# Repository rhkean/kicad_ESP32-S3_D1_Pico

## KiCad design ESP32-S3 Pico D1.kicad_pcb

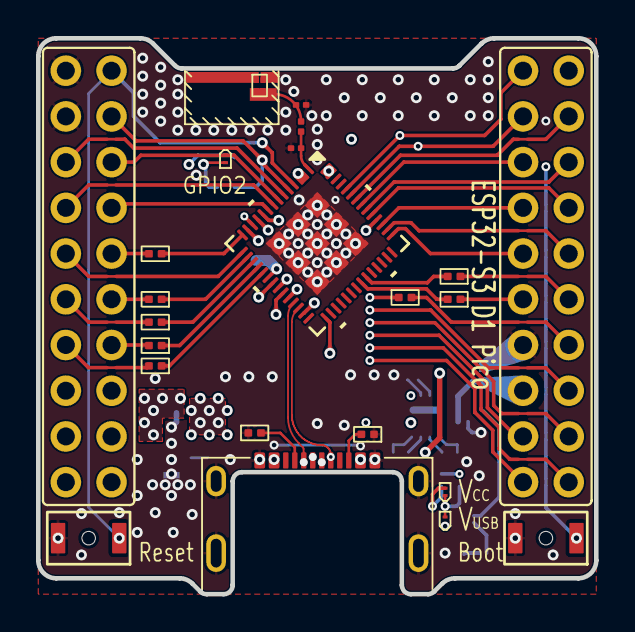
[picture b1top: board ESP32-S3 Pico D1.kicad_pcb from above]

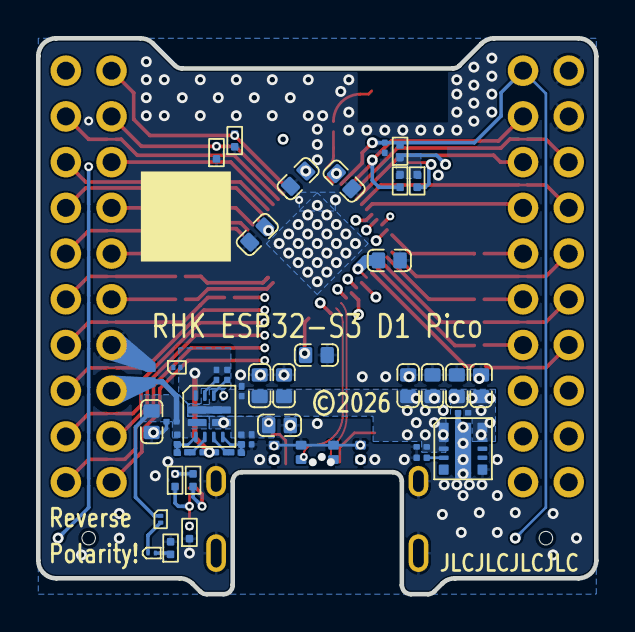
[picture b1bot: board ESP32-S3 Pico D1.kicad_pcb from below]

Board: 6 copper layers, 31.0 x 30.9 mm, 69 parts (47 on the bottom side), 65 nets.

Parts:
ANT401: 2450AT07A0100; Chip Antenna 0402
C401, C402, C403, C404, C405, C501, C503, C507, C508, C509, C510, C513, C514: 22uF; C_0603_Dense
C406, C407: DNP; C_0201_Dense
C502, C504, C505, C506, C511, C512, C601: 0.1uF; C_0201_Dense
CN501: GT-USB-7014D; USB_C_Receptacle_G-Switch-GT-USB-7014D
D501, D502, D505: D15V0H1U2LP-7B; DFN1006-2
D503, D504: SZESD7241N2T5G; DFN1006-2
D506, D601: PMEG4002ESFYL; DFN0603-2
LED601: Blue; LED_0201-2
LED602: Green; LED_0201-2
LED603: Orange; LED_0201-2
LED604: Red; LED_0201-2
R401, R402, R403, R404, R405, R406, R407, R408: 33R; R_0201_Nominal
R409, R410, R501, R502, R601, R602, R604, R605, R606: 5k1; R_0201_Nominal
R411: 0R; R_0201_Dense
R503, R506, R509: 100k; R_0201_Dense
R504, R505, R507, R508, R510: 26k1; R_0201_Dense
R603, R607: 470R; R_0201_Nominal
SW601, SW602: SPST-NO; SW_SPST_B3U_series
U201: ESP32-S3_D1_Pico
U401: ESP32-S3-PICO-1-N8R2; ESP32-S3-Pico-1
U501: TPS2121; VQHN-HR-12
U502: TPSM82903; uSIP-11_3.0x2.8

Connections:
/+5V_{EXT}: C501.1, C502.1, D505.1 (K), D601.1 (K), R506.1, U201.28 (+5V_{EXT}), U501.2 (IN2)
/ESP32-S3 Pico D1-Main/+3V3: C401.1, C402.1, C403.1, C404.1, C405.1, C512.1, C513.1, C514.1, R601.1, R602.1, R603.1, R604.2, R606.2, U201.8 (+3V3_{out}), U201.18 (+3V3), U401.2 (VDD3P3), U401.3 (VDD3P3), U401.20 (VDD3P3_RTC), U401.29 (VDD_SPI), U401.46 (VDD3P3_CPU), U401.55 (VDDA), U401.56 (VDDA), U502.9 (VOUT), U502.10 (VOUT)
/ESP32-S3 Pico D1-Main/+5V_{FUSED}: C506.1, C507.1, C508.1, C509.1, C510.1, C511.1, U201.9 (+5V_{FUSED_{out}}), U501.1 (OUT), U501.8 (OUT), U502.1 (VIN), U502.2 (VIN), U502.3 (EN)
/ESP32-S3 Pico D1-Main/EN/~Reset: C601.1, R601.2, SW601.1, U201.11 (EN/~RST), U401.4 (CHIP_PU)
/ESP32-S3 Pico D1-Main/ESP32-S3-PICO-1/GPIO09: R401.1, U401.14 (GPIO09)
/ESP32-S3 Pico D1-Main/ESP32-S3-PICO-1/GPIO11: R402.1, U401.16 (GPIO11)
/ESP32-S3 Pico D1-Main/ESP32-S3-PICO-1/GPIO12: R403.1, U401.17 (GPIO12)
/ESP32-S3 Pico D1-Main/ESP32-S3-PICO-1/GPIO13: R404.1, U401.18 (GPIO13)
/ESP32-S3 Pico D1-Main/ESP32-S3-PICO-1/GPIO14: R405.1, U401.19 (GPIO14)
/ESP32-S3 Pico D1-Main/ESP32-S3-PICO-1/GPIO21: R406.1, U401.27 (GPIO21)
/ESP32-S3 Pico D1-Main/ESP32-S3-PICO-1/RF_Feed: ANT401.1 (Feed), ANT401.4 (Feed), C407.1, R411.2
/ESP32-S3 Pico D1-Main/ESP32-S3-PICO-1/RF_In: C406.1, R411.1, U401.1 (LNA_IN)
/ESP32-S3 Pico D1-Main/ESP32-S3-PICO-1/USB_D+: CN501.A6 (D+), CN501.B6 (D+), D503.1 (A1), U401.26 (GPIO20/USB_D+)
/ESP32-S3 Pico D1-Main/ESP32-S3-PICO-1/USB_D-: CN501.A7 (D-), CN501.B7 (D-), D504.1 (A1), U401.25 (GPIO19/USB_D-)
/ESP32-S3 Pico D1-Main/IO00: R602.2, SW602.1, U201.12 (IO00), U401.5 (GPIO00)
/ESP32-S3 Pico D1-Main/IO01: U201.3 (IO01), U401.6 (GPIO01)
/ESP32-S3 Pico D1-Main/IO02: LED601.1 (K), U201.13 (IO02), U401.7 (GPIO02)
/ESP32-S3 Pico D1-Main/IO03: U201.4 (IO03), U401.8 (GPIO03)
/ESP32-S3 Pico D1-Main/IO04: U201.14 (IO04), U401.9 (GPIO04)
/ESP32-S3 Pico D1-Main/IO05: U201.20 (I005), U401.10 (GPIO05)
/ESP32-S3 Pico D1-Main/IO06: U201.19 (IO06), U401.11 (GPIO06)
/ESP32-S3 Pico D1-Main/IO07: U201.10 (IO07), U401.12 (GPIO07)
/ESP32-S3 Pico D1-Main/IO08: U201.30 (IO08), U401.13 (GPIO08)
/ESP32-S3 Pico D1-Main/IO09: R401.2, U201.15 (IO09)
/ESP32-S3 Pico D1-Main/IO10: U201.5 (IO10), U401.15 (GPIO10)
/ESP32-S3 Pico D1-Main/IO11: R402.2, U201.16 (IO11)
/ESP32-S3 Pico D1-Main/IO12: R403.2, U201.6 (IO12)
/ESP32-S3 Pico D1-Main/IO13: R404.2, U201.17 (IO13)
/ESP32-S3 Pico D1-Main/IO14: R405.2, U201.7 (IO14)
/ESP32-S3 Pico D1-Main/IO15: U201.40 (IO15), U401.21 (XTAL_32K_P/GPIO15)
/ESP32-S3 Pico D1-Main/IO16: U201.39 (IO16), U401.22 (XTAL_32K_N/GPIO16)
/ESP32-S3 Pico D1-Main/IO17: U201.29 (IO17), U401.23 (GPIO17)
/ESP32-S3 Pico D1-Main/IO18: U201.38 (IO18), U401.24 (GPIO18)
/ESP32-S3 Pico D1-Main/IO21: R406.2, U201.37 (IO21)
/ESP32-S3 Pico D1-Main/IO38: U201.25 (IO38), U401.43 (GPIO38)
/ESP32-S3 Pico D1-Main/IO39: U201.35 (IO39), U401.44 (MTCK/GPIO39)
/ESP32-S3 Pico D1-Main/IO40: U201.24 (IO40), U401.45 (MTDO/GPIO40)
/ESP32-S3 Pico D1-Main/IO41: U201.34 (IO41), U401.47 (MTDI/GPIO41)
/ESP32-S3 Pico D1-Main/IO42: U201.33 (IO42), U401.48 (MTMS/GPIO42)
/ESP32-S3 Pico D1-Main/IO43: U201.23 (IO43), U401.49 (U0TXD/GPIO43)
/ESP32-S3 Pico D1-Main/IO44: U201.32 (IO44), U401.50 (U0RXD/GPIO44)
/ESP32-S3 Pico D1-Main/IO45: R409.2, U201.22 (IO45), U401.51 (GPIO45)
/ESP32-S3 Pico D1-Main/IO46: R410.2, U201.21 (IO46), U401.52 (GPIO46)
/ESP32-S3 Pico D1-Main/IO47: R407.1, U201.36 (IO47)
/ESP32-S3 Pico D1-Main/IO48: R408.1, U201.26 (IO48)
/ESP32-S3 Pico D1-Main/USB_Power_Interface/+V_{BUS}: C503.1, C504.1, CN501.A4 (VBUS), CN501.A9 (VBUS), CN501.B4 (VBUS), CN501.B9 (VBUS), D501.1 (K), D502.1 (K), R503.1, U501.7 (IN1)
/ESP32-S3 Pico D1-Main/USB_Power_Interface/CC1: CN501.A5 (CC1), R502.2
/ESP32-S3 Pico D1-Main/USB_Power_Interface/CC2: CN501.B5 (CC2), R501.2
/ESP32-S3 Pico D1-Main/USB_Power_Interface/CP2: R506.2, R507.2, U501.3 (CP2)
/ESP32-S3 Pico D1-Main/USB_Power_Interface/GND1: C505.2, D506.2 (A), R505.1, R508.1, R509.2, U501.12 (GND)
/ESP32-S3 Pico D1-Main/USB_Power_Interface/ILM: R509.1, U501.10 (ILM)
/ESP32-S3 Pico D1-Main/USB_Power_Interface/OV1: R504.1, R505.2, U501.5 (OV1)
/ESP32-S3 Pico D1-Main/USB_Power_Interface/OV2: R507.1, R508.2, U501.4 (OV2)
/ESP32-S3 Pico D1-Main/USB_Power_Interface/PR1: R503.2, R504.2, U501.6 (PR1)
/ESP32-S3 Pico D1-Main/USB_Power_Interface/Pwr Src Ind: LED602.2 (A), LED603.1 (K), R604.1, U501.9 (ST)
/ESP32-S3 Pico D1-Main/USB_Power_Interface/SCONFd: R510.2, U502.4 (SCONF)
/ESP32-S3 Pico D1-Main/USB_Power_Interface/SS: C505.1, U501.11 (SS)
/ESP32-S3 Pico D1-Main/User Interface/LED1_H: LED603.2 (A), R606.1
/ESP32-S3 Pico D1-Main/User Interface/LED2_H: LED601.2 (A), R603.2
/ESP32-S3 Pico D1-Main/User Interface/LED3_L: LED602.1 (K), R605.2
/ESP32-S3 Pico D1-Main/User Interface/LED4_H: LED604.2 (A), R607.1
/ESP32-S3 Pico D1-Main/User Interface/LED4_L: D601.2 (A), LED604.1 (K)
/GND: ANT401.2 (GND), ANT401.3 (GND), C401.2, C402.2, C403.2, C404.2, C405.2, C406.2, C407.2, C501.2, C502.2, C503.2, C504.2, C506.2, C507.2, C508.2, C509.2, C510.2, C511.2, C512.2, C513.2, C514.2, C601.2, CN501.A1 (GND), CN501.A12 (GND), CN501.B1 (GND), CN501.B12 (GND), CN501.S1 (SHIELD), CN501.S2 (SHIELD), CN501.S3 (SHIELD), CN501.S4 (SHIELD), D501.2 (A), D502.2 (A), D503.2 (A2), D504.2 (A2), D505.2 (A), D506.1 (K), R409.1, R410.1, R501.1, R502.1, R510.1, R605.1, R607.2, SW601.2, SW602.2, U201.1 (GND), U201.2 (GND), U201.27 (GND), U401.57 (GND), U502.6 (PG), U502.11 (GND)
unnamed: R408.2, U401.36 (SPICLK_N/GPIO48)
unnamed: R407.2, U401.37 (SPICLK_P/GPIO47)

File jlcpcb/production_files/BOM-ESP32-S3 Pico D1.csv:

Comment,Designator,Footprint,LCSC,Quantity
0.1uF,"C502,C504,C505,C506,C511,C512,C601",C_0201_Dense,C915760,7
0R,R411,R_0201_Dense,C473473,1
100k,"R503,R506,R509",R_0201_Dense,C226394,3
22uF,"C401,C402,C403,C404,C405,C501,C503,C507,C508,C509,C510,C513,C514",C_0603_Dense,C29519229,13
2450AT07A0100,ANT401,Chip Antenna 0402,C17531353,1
26k1,"R504,R505,R507,R508,R510",R_0201_Dense,C910625,5
33R,"R401,R402,R403,R404,R405,R406,R407,R408",R_0201_Nominal,C226514,8
470R,"R603,R607",R_0201_Nominal,C226558,2
5k1,"R409,R410,R501,R502,R601,R602,R604,R605,R606",R_0201_Nominal,C226588,9
Blue,LED601,LED_0201-2,C3646921,1
D15V0H1U2LP-7B,"D501,D502,D505",DFN1006-2,C1973850,3
ESP32-S3-PICO-1-N8R2,U401,ESP32-S3-Pico-1,C7558093,1
GT-USB-7014D,CN501,USB_C_Receptacle_G-Switch-GT-USB-7014D,C2843969,1
Green,LED602,LED_0201-2,C3646922,1
Orange,LED603,LED_0201-2,C5440629,1
PMEG4002ESFYL,"D506,D601",DFN0603-2,C22435168,2
Red,LED604,LED_0201-2,C3646923,1
SPST-NO,"SW601,SW602",SW_SPST_B3U_series,C4364471,2
SZESD7241N2T5G,"D503,D504",DFN1006-2,C604770,2
TPS2121,U501,VQHN-HR-12,C485916,1
TPSM82903,U502,uSIP-11_3.0x2.8,C6290583,1

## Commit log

2026-03-13 streamlined routing by discarding legacy GPIO pinout compatibility. reduced Vin to Vcc and Vbus (no more +16V) includes CAN & Vehicle inputs (need to move to 2nd board, though) added wake-on-start by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
2026-03-13 Add backup and history folders to .gitignore
2026-03-25 Update .gitignore, BOM-ESP32-S3 Pico D1.csv, CANBus_Interface.kicad_sch, and 14 more files
2026-03-26 removed BOM-ESP32-S3 Pico D1.csv, created WLED_UnderGlow_AI_Skill.md, BOM_Sync_Skill.md and ai-instructions.md CoPilot configurations WLED UnderGLow.md updated WLED\ UnderGlow.md
2026-04-23 Update CANBus_Interface.kicad_sch, ESP32-S3 D1 Pico Board.kicad_sch, ESP32-S3 Pico D1.kicad_pcb, and 15 more files
2026-05-06 Update CAN_Interface.kicad_sch, ESP32-S3 D1 Pico Board.kicad_sch, ESP32-S3 Pico D1.kicad_pcb, and 5 more files
2026-05-06 removed CANBus_Interface.kicad_sch, CAN_Interface.kicad_sch, GR86_Inputs.kicad_sch, and 3 more files
2026-05-06 remove documents from project folder
2026-05-07 fixed hierarchical sheets; replaced pin headers with ESP32-S3_D1_Pico symbol
2026-05-07 added new ESP32-S3 D1 Pico symbol and footprint
2026-06-05 Update ESP32-S3 Pico D1-Main.kicad_sch, ESP32-S3 Pico D1.kicad_pcb, ESP32-S3 Pico D1.kicad_prl, and 7 more files
2026-06-14 JLCPCB: W2026060405431160 2026-06-03 PCB: Y61-5297522A PCBA: SMT026060363646-5297522A

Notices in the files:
ESP32-S3 Pico D1.kicad_pcb:
©2026
